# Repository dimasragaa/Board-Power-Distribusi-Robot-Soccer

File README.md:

# Board-Power-Distribusi-Robot-Soccer

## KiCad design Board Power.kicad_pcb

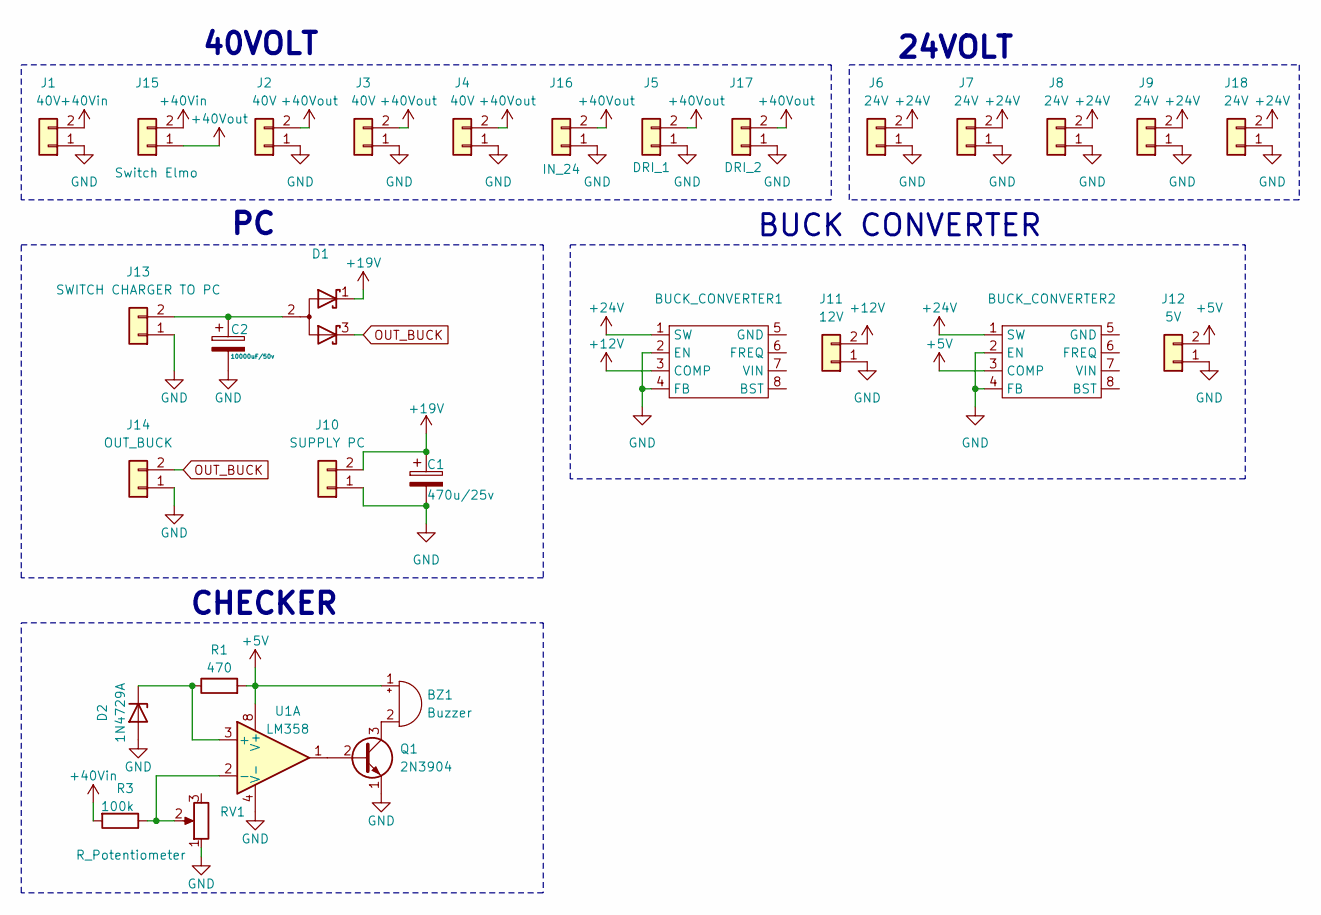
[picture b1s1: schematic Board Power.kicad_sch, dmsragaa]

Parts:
BUCK_CONVERTER1, BUCK_CONVERTER2: MP1584
BZ1: Buzzer; Buzzer_12x9.5RM7.6
C1: 470u/25v; C_Elec_10x10.2
C2: 10000uF/50v; CP_Radial_D30.0mm_P10.00mm_SnapIn
D1: D_Schottky_Dual_CommonAnode_KAK_Parallel; TO-220-3_Vertical
D2: 1N4729A; D_DO-41_SOD81_P10.16mm_Horizontal
J1, J2, J3, J4: 40V; XT90
J5: DRI_1; AMASS_XT60-M_1x02_P7.20mm_Vertical
J6, J7, J8, J9: 24V; AMASS_XT60-M_1x02_P7.20mm_Vertical
J10: SUPPLY PC; AMASS_XT30U-M_1x02_P5.0mm_Vertical
J11: 12V; JST_XH_B2B-XH-A_1x02_P2.50mm_Vertical
J12: 5V; JST_XH_B2B-XH-A_1x02_P2.50mm_Vertical
J13: SWITCH CHARGER TO PC; AMASS_XT30U-M_1x02_P5.0mm_Vertical
J14: OUT_BUCK; AMASS_XT30U-M_1x02_P5.0mm_Vertical
J15: Switch Elmo; TerminalBlock_Phoenix_MKDS-1,5-2-5.08_1x02_P5.08mm_Horizont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
J16: IN_24; AMASS_XT60-M_1x02_P7.20mm_Vertical
J17: DRI_2; AMASS_XT60-M_1x02_P7.20mm_Vertical
J18: 24V; AMASS_XT30U-M_1x02_P5.0mm_Vertical
Q1: 2N3904; TO-92_Inline
R1: 470; R_0805_2012Metric
R3: 100k; R_0805_2012Metric
RV1: R_Potentiometer; Potentiometer_Bourns_3296W_Vertical
U1: LM358; DIP-8_W7.62mm

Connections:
+5V: BUCK_CONVERTER2.3 (COMP), BZ1.1 (+), J12.2, R1.2, U1.8 (V+)
+12V: BUCK_CONVERTER1.3 (COMP), J11.2
+19V: C1.1, D1.1 (K), J10.2
+24V: BUCK_CONVERTER1.1 (SW), BUCK_CONVERTER2.1 (SW), J6.2, J7.2, J8.2, J9.2, J18.2
+40Vin: J1.2, J15.2, R3.2
+40Vout: J2.2, J3.2, J4.2, J5.2, J15.1, J16.2, J17.2
GND: BUCK_CONVERTER1.2 (EN), BUCK_CONVERTER1.4 (FB), BUCK_CONVERTER2.2 (EN), BUCK_CONVERTER2.4 (FB), C1.2, C2.2, D2.2 (A), J1.1, J2.1, J3.1, J4.1, J5.1, J6.1, J7.1, J8.1, J9.1, J10.1, J11.1, J12.1, J13.1, J14.1, J16.1, J17.1, J18.1, Q1.1 (E), RV1.1, U1.4 (V-)
unnamed: BZ1.2 (-), Q1.3 (C)
unnamed: C2.1, D1.2 (A), J13.2
unnamed: D2.1 (K), R1.1, U1.3 (+)
unnamed: Q1.2 (B), U1.1
unnamed: R3.1, RV1.2, U1.2 (-)
OUT_BUCK: D1.3 (K), J14.2

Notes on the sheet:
24VOLT
40VOLT
BUCK CONVERTER
CHECKER

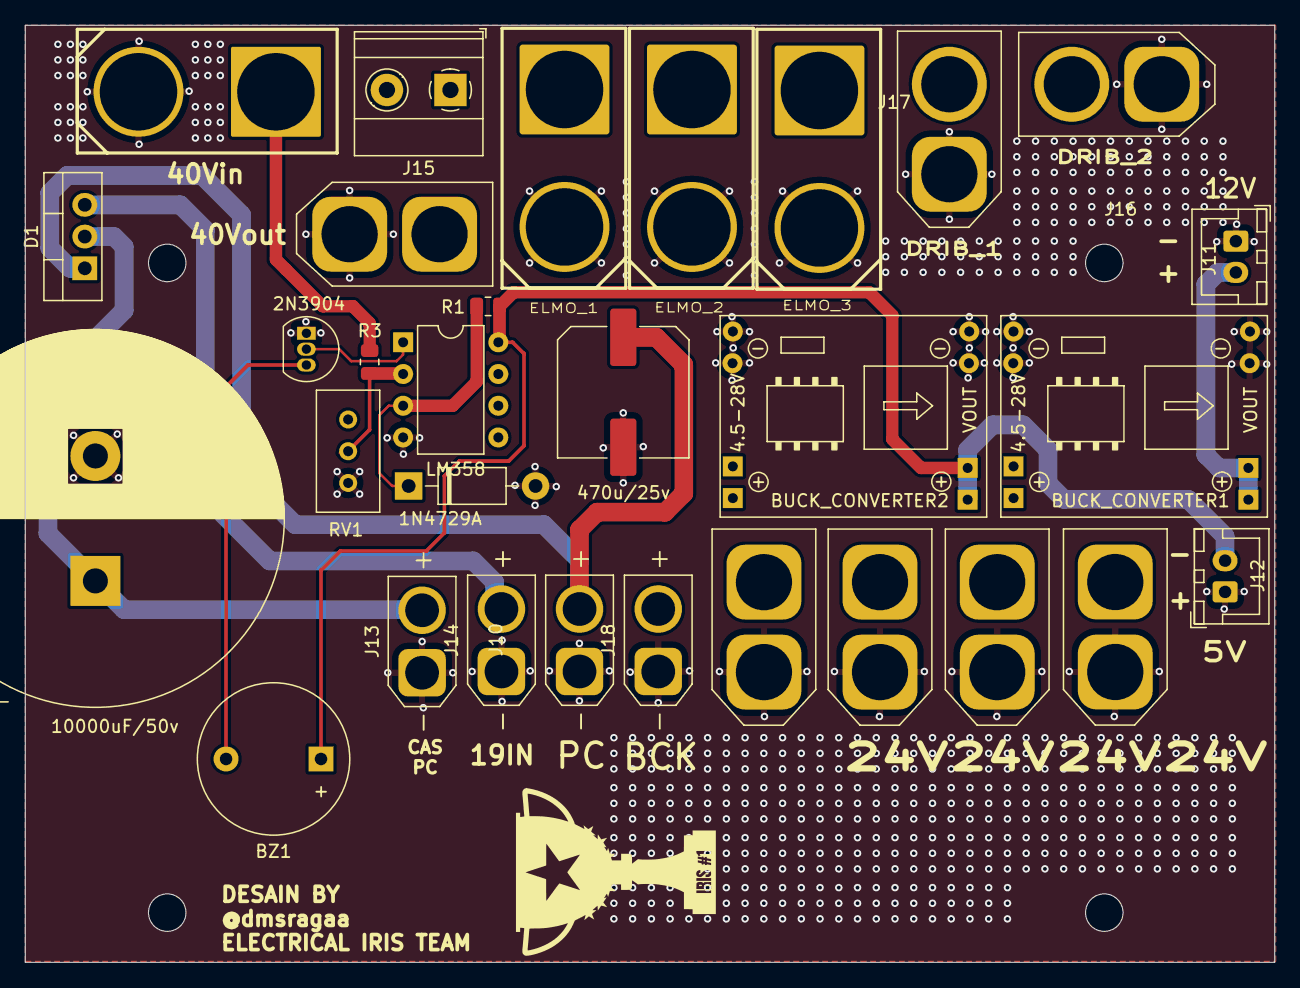
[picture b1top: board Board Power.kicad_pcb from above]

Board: 2 copper layers, 100.0 x 75.0 mm, 30 parts (0 on the bottom side), 13 nets.

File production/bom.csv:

Designator,Footprint,Quantity,Value,LCSC Part #
"BUCK_CONVERTER1, BUCK_CONVERTER2",MP1584,2,~,
BZ1,Buzzer_12x9.5RM7.6,1,Buzzer,
C1,C_Elec_10x10.2,1,470u/25v,
C2,CP_Radial_D30.0mm_P10.00mm_SnapIn,1,10000uF/50v,
D1,TO-220-3_Vertical,1,D_Schottky_Dual_CommonAnode_KAK_Parallel,
D2,D_DO-41_SOD81_P10.16mm_Horizontal,1,1N4729A,
"J1, J2, J3, J4",XT90,4,40V,
J10,AMASS_XT30U-M_1x02_P5.0mm_Vertical,1,SUPPLY PC,
J11,JST_XH_B2B-XH-A_1x02_P2.50mm_Vertical,1,12V,
J12,JST_XH_B2B-XH-A_1x02_P2.50mm_Vertical,1,5V,
J13,AMASS_XT30U-M_1x02_P5.0mm_Vertical,1,SWITCH CHARGER TO PC,
J14,AMASS_XT30U-M_1x02_P5.0mm_Vertical,1,OUT_BUCK,
J15,"TerminalBlock_Phoenix_MKDS-1,5-2-5.08_1x02_P5.08mm_Horizontal",1,Switch Elmo,
J16,AMASS_XT60-M_1x02_P7.20mm_Vertical,1,IN_24,
J17,AMASS_XT60-M_1x02_P7.20mm_Vertical,1,DRI_2,
J18,AMASS_XT30U-M_1x02_P5.0mm_Vertical,1,24V,
J5,AMASS_XT60-M_1x02_P7.20mm_Vertical,1,DRI_1,
"J6, J7, J8, J9",AMASS_XT60-M_1x02_P7.20mm_Vertical,4,24V,
Q1,TO-92_Inline,1,2N3904,
R1,0805,1,470,
R3,0805,1,100k,
RV1,Potentiometer_Bourns_3296W_Vertical,1,R_Potentiometer,
U1,DIP-8_W7.62mm,1,LM358,
